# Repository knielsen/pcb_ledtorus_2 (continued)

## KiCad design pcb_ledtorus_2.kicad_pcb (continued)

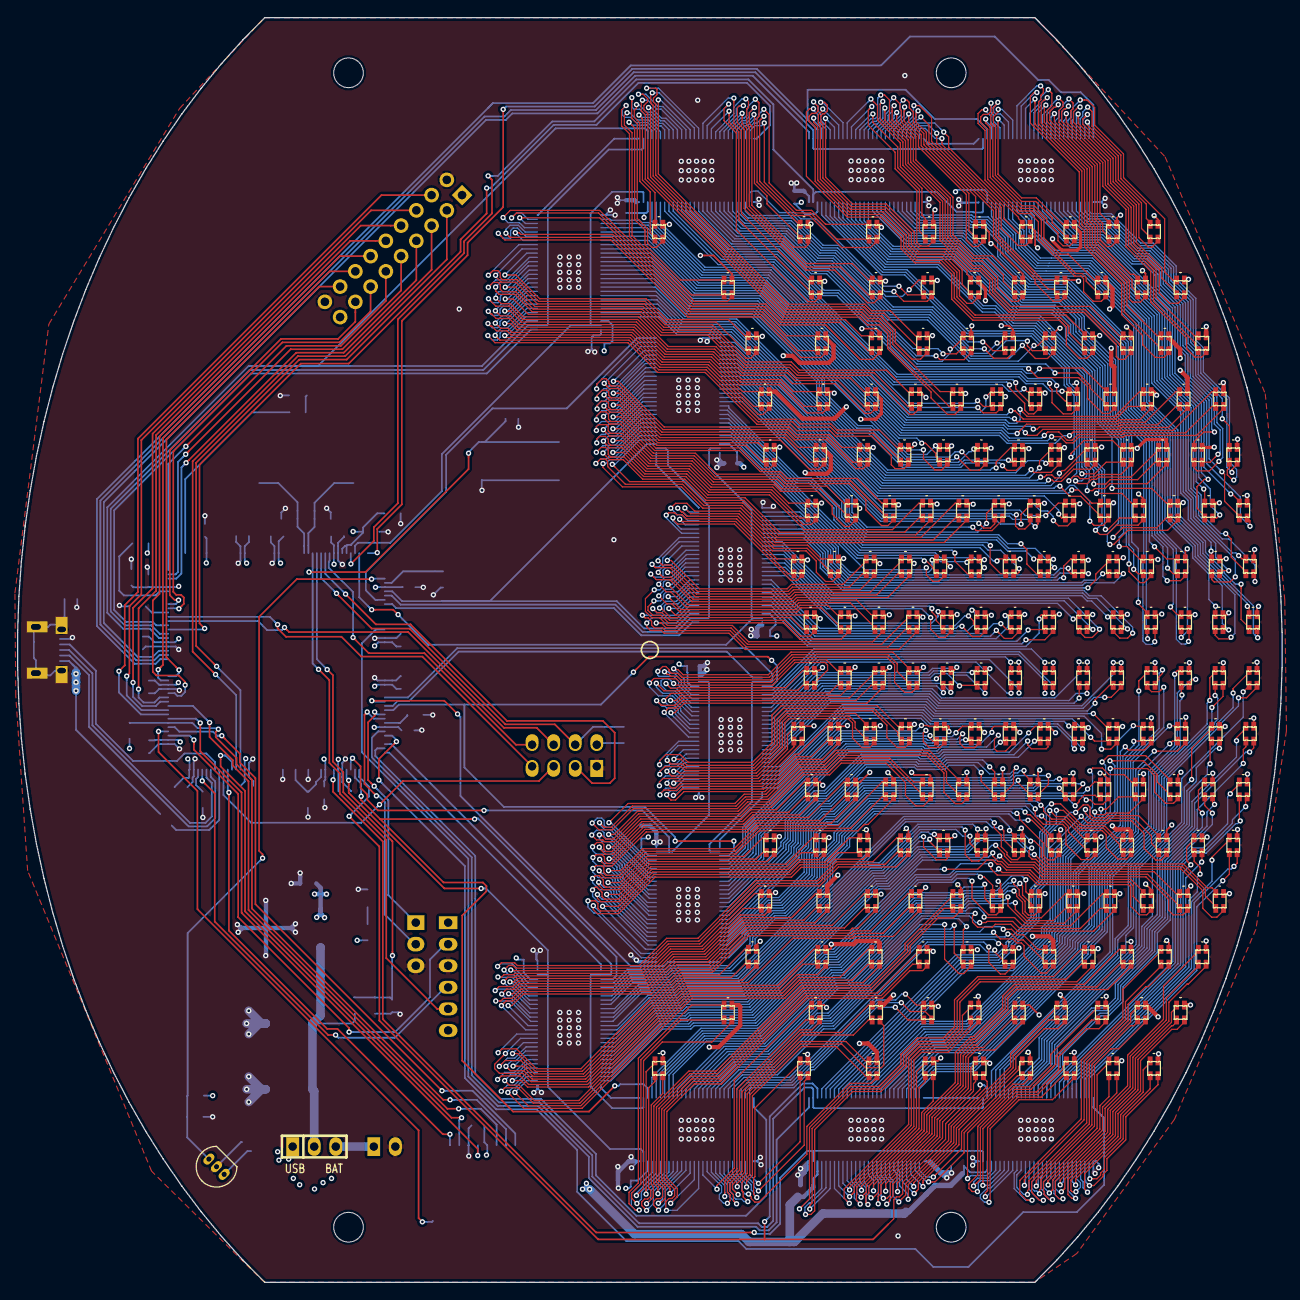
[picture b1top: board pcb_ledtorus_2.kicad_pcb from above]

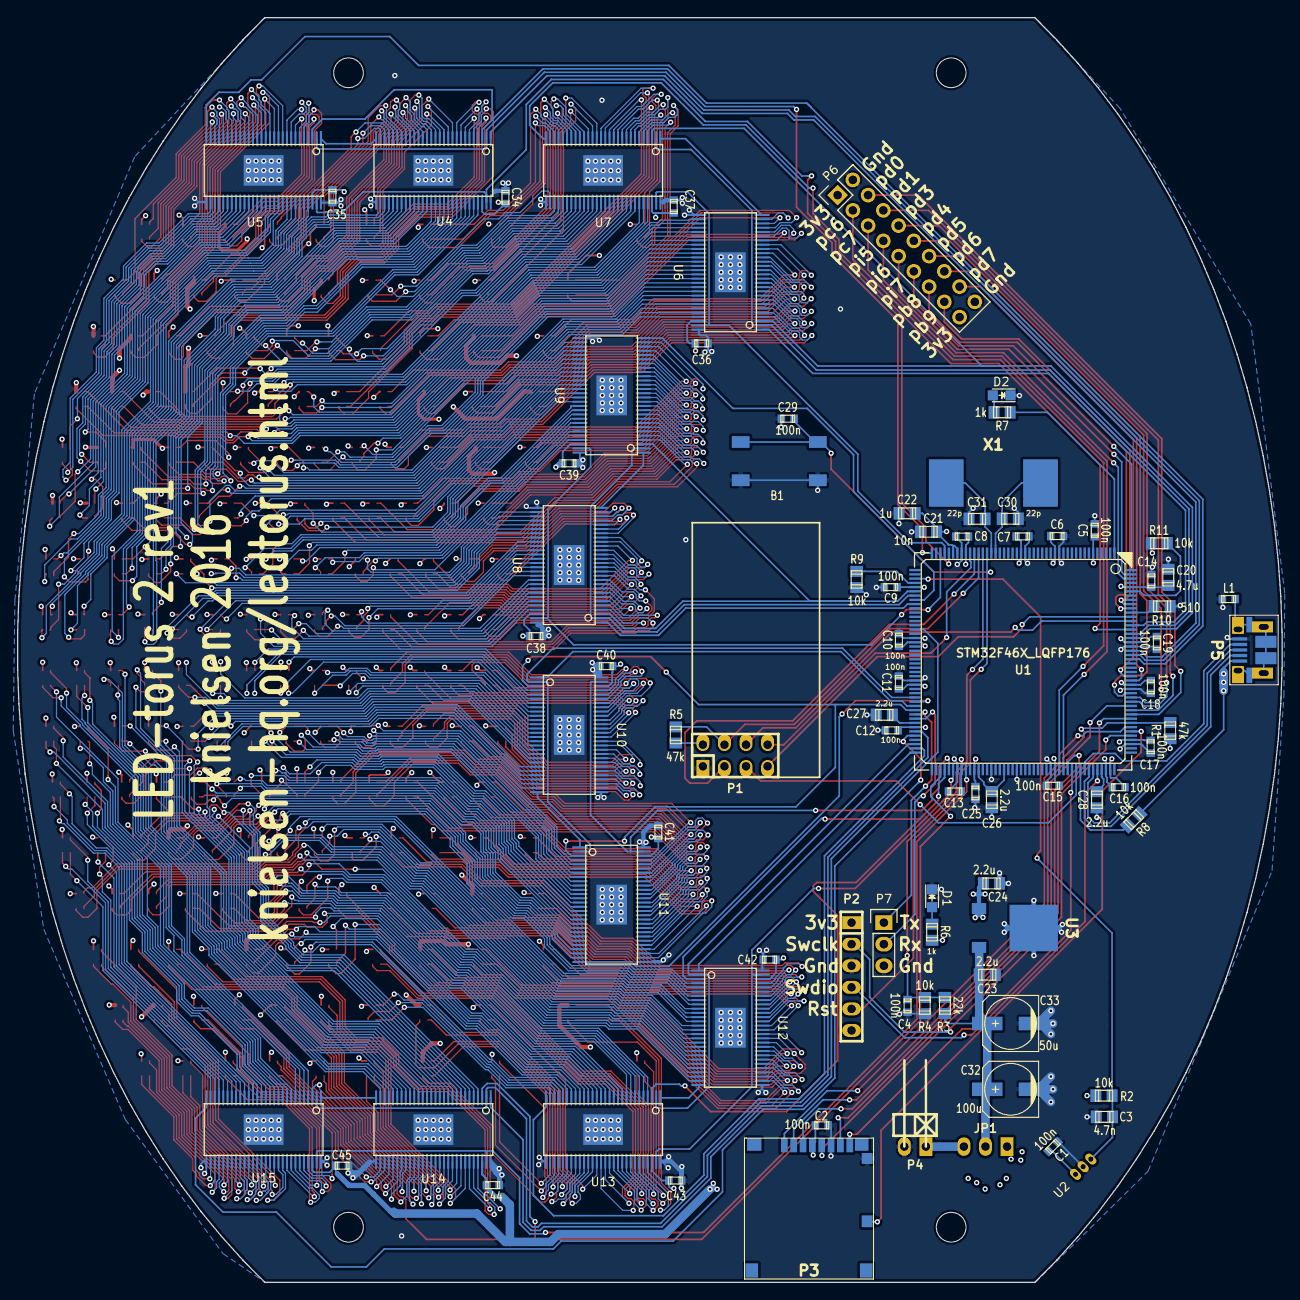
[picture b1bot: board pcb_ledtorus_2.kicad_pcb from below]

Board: 4 copper layers, 149.0 x 149.0 mm, 276 parts (82 on the bottom side), 667 nets.

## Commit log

2015-11-01 Initial draft of PCB for LED-torus 2
    Some basic stuff done, not complete/checked yet.
    LEDs and TLCs still missing.
2015-11-01 First draft of LEDs schematics sheet.
    Needs some processing to get numbering right, easier to do with some
    scripting.
2015-11-02 Fix sin/sclk/sout/lat/gsclk 1-6 pins and labels.
2015-11-02 Fix alignment of everything to 50 mil
2015-11-02 Assign labels led{1..192}{r,g,b} to all LED pins.
    (This is just an intermediate assignment to TLC outputs; real
    assignments will be determined later, according to what works best for
    the PCB routing).
2015-11-02 Misc. small fixes, DRC (almost) passes now.
2015-11-03 Couple small fixes and tweaks.
    Some resistors added on inputs connected directly to power lines.
    Few labels added.
2015-11-03 Basic netlist with footprint assignment and import into pcbnew
2015-11-03 Place LEDs for PCB routing.
2015-11-03 Add elliptical board outline
2015-11-03 Add power planes
2015-11-03 Move a couple footprints out a bit.
2015-11-03 Component PCB sides, and 3d models.
2015-11-04 Couple small tweaks, 3d shapes.
2015-12-31 Some experiments with a way to route the LEDs
2016-02-16 Intermediate commit
2016-03-08 Some partial ideas for LEDs and TLCs placement and routing.
2016-03-15 Good progress on LED routing.
    Upper half now routed with 6/6 mil tracks/clearance.
    Still need to fit 5V vias for all LEDs, hopefully vias can find room.
    Looks promising - if everything works, lower half should be doable the
    same way.
2016-03-15 Some routing of LEDs VCC.
    It's tight, but it looks possible.
2016-03-16 First reasonably complete routing of upper half of LEDs.
    All LEDs have vias to power plane now. And TLCs have power and de-coupling.
    Everything seems to fit, just.
2016-03-17 Small component changes.
    Fix couple of missing footprints. Make 100nF caps 0603.
    Some very rough component placement to avoid overlap.
2016-03-17 Fix so that DRC passes (with lots of unconnected)
2016-03-17 First rough component placement, looks ok.
2016-03-18 Some preliminary routing of signals between TLCs and MCU.
    Mostly to check that everything looks reasonably possible.
2016-03-18 Rip out all LED routing in lower half in preparation for proper routing like top half.
2016-03-18 Fix LED-mapping for lower half to match upper half.
    (In schematics and netlist).
2016-03-18 Back TLC part of lower half of LEDs routed.
2016-03-19 Complete routing of LEDs.
    Probably a good idea to do some additional cleanup, but it seems
    already reasonable.
2016-03-19 Some cleanup of the LED routing.
2016-03-19 More LED cleanup routing.
2016-03-19 More LED routing cleanup
2016-03-21 Preliminary routing of most remaning signals.
2016-03-23 First version that fully passes DRC.
    Still some polishing to do (like extra GPIO header, general cleanup, ...).
2016-03-24 Fix LED polarity (+ small cleanups).
2016-03-24 Cleanup back routing on U6 (looks much improved, really).
2016-03-24 Cleanup back routing on U5
2016-03-24 Cleanup back routing on U4
2016-03-24 More cleanups above LEDs
2016-03-24 Cleanup back routing on U7
2016-03-24 Cleanup back routing on U9
2016-03-24 Cleanup back routing on U8
2016-03-24 Cleanup back routing on U10
2016-03-24 Cleanup back routing on U11
2016-03-24 Cleanup back routing on U12
2016-03-24 Cleanup back routing on U13
2016-03-25 Cleanup back routing on U14
2016-03-25 Cleanup back routing on U15
2016-03-26 Some misc. small LED routing cleanups.
2016-03-27 Create new GPIO header.
    Has 14 GPIOs with reasonable availability of peripherals (timers, usarts, ...).
    The location is in upper left; USB is moved to the middle left.
    (Neither USB nor generic GPIO are expected to be populated on the
    actual LED-torus, but could turn out useful for other purposes).
    Routing for this is preliminary, needs cleanup.
2016-03-27 Move decoupling caps as close to the MCU as possible.
2016-03-27 Cleanup GPIO routing
2016-03-27 Rotate nRF 180 degrees, and cleanup the routing a bit.
2016-03-27 Switch user LED to PE2.
    (PC13, as it was before, has limited current sink capabilities).
2016-03-27 Misc. routing cleanup.
2016-03-27 More routing cleanup. Starting to look good now.
2016-03-27 Small tweaks in routing.
2016-03-28 Remove incorrect routing of PB2 as SWO.
    Also some misc. routing cleanups.
2016-03-28 Remove stray non-default grid origin
2016-03-28 Fix silk screen.
2016-03-29 Initial gerber generation
2016-03-29 Move usb to back side of pcb.
2016-04-10 Final gerbers for rev1
